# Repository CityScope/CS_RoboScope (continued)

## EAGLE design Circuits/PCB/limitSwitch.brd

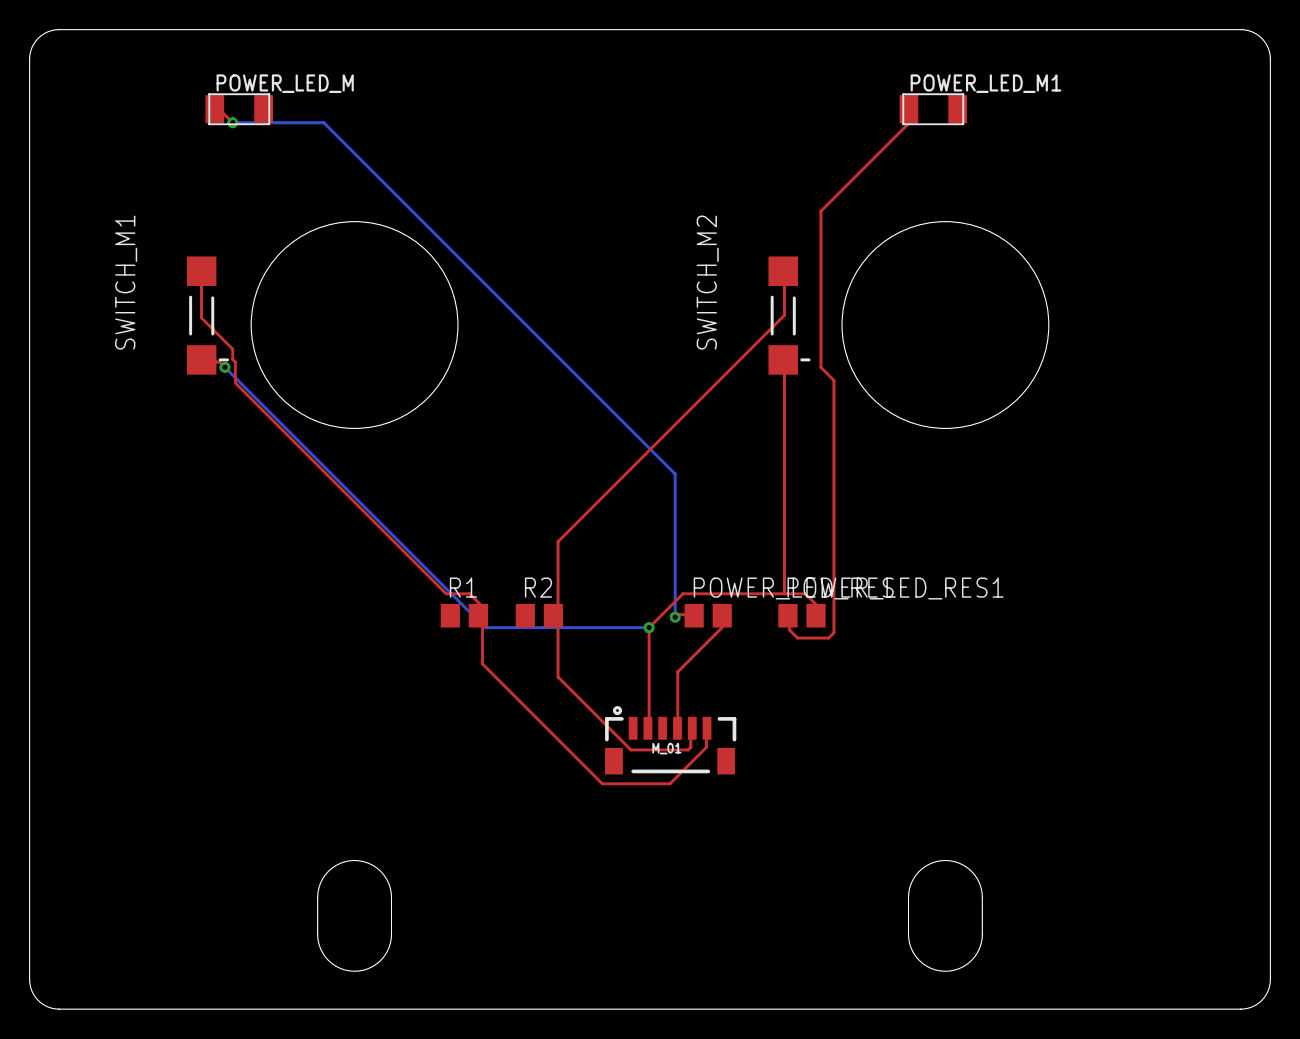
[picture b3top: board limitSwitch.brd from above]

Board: 2 copper layers, 84.0 x 66.3 mm, 9 parts (0 on the bottom side), 7 nets.

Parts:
M_01: 1X06-1MM
POWER_LED_M, POWER_LED_M1: LEDFAB1206; LED1206FAB
POWER_LED_RES, POWER_LED_RES1: 500; M0805
R1, R2: 10k; M0805
SWITCH_M1, SWITCH_M2: DTSM-3

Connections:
GND_MCU: M_01.1, POWER_LED_M.2, POWER_LED_M1.2, R1.1, R2.1
LED_IN: M_01.4, POWER_LED_RES.2
unnamed: POWER_LED_M1.1, POWER_LED_RES1.1
unnamed: POWER_LED_M.1, POWER_LED_RES.1
SWITCH_01: M_01.6, R1.2, SWITCH_M1.2
SWITCH_02: M_01.5, R2.2, SWITCH_M2.2
VCC_MCU: M_01.2, POWER_LED_RES1.2, SWITCH_M1.1, SWITCH_M2.1

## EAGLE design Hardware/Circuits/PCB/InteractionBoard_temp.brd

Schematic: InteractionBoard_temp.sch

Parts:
C1, C2, C3, C4, C5, C6, C7, C8, C9: 0.1uF; 0603-CAP
J3: F-2X10-DIL-2MM; DIL-2MM-2X10
JP1: JUMPER-SMT_3_1-NC_TRACE_NO-SILK; SMT-JUMPER_3_1-NC_TRACE_NO-SILK
JP6, JP7, JP8, JP9, JP10, JP11: JUMPER-SMT_2_NC_TRACE_NO-SILK; SMT-JUMPER_2_NC_TRACE_NO-SILK
M_01, M_02, M_03, M_04, M_05, M_06, M_07, M_08: CONN_06SMD-1MM; 1X06-1MM
POWE_3.3: LEDFAB1206; LED1206FAB
R1, R2, R3, R5, R6, R7, R8: 10k; M0805
R4: 10K; M0805
R9, R10, R11, R12, R13, R14, R16, R17, R18, R19, R20, R21, R23, R24, R25, R26: 10K; 0603-RES
R27, R28: 500; 0603-RES
RN1, RN2, RN3: 4R-NEXB38V; EXB38V
S1: JS207011SCQNR; SW_JS207011SCQNR
S2: MOMENTARY-SWITCH-SPST-2-SMD-5.2MM; TACTILE_SWITCH_SMD_5.2MM
STATUS_LED: LEDFAB1206; LED1206FAB
SW1: 219-10; CTS-219-10
SWB_1, SWB_2, SWB_3, SWB_4, SWB_5, SWB_6, SWB_7, SWB_8: B3F-1000
SWITCH_M1, SWITCH_M2, SWITCH_M3, SWITCH_M4, SWITCH_M5, SWITCH_M6, SWITCH_M7, SWITCH_M8: DTSM-3
SWR_1, SWR_2, SWR_3, SWR_4, SWR_5, SWR_6, SWR_7, SWR_8: 10K; M0805
U1, U2, U4: SX1509; QFN-28

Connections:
0_SX1: M_04.6, U1.27 (I/O[0])
0_SX2: M_08.6, U2.27 (I/O[0])
0_SX3: U4.27 (I/O[0])
1_SX1: M_04.5, U1.28 (I/O[1])
1_SX2: M_08.5, U2.28 (I/O[1])
1_SX3: J3.16, U4.28 (I/O[1])
2_SX1: M_02.6, U1.1 (I/O[2])
2_SX2: M_06.6, U2.1 (I/O[2])
2_SX3: J3.14, U4.1 (I/O[2])
3.3V: C1.1, C2.1, C3.1, C4.1, C5.1, C6.1, C7.1, C8.1, C9.1, J3.19, R9.2, R10.2, R11.2, R12.2, R13.2, R14.2, R16.2, R17.2, R18.2, R19.2, R20.2, R21.2, R23.2, R24.2, R25.2, R26.2, R27.2, RN1.5 (2), RN1.6 (2), RN1.7 (2), RN1.8 (2), RN2.7 (2), RN2.8 (2), RN3.5 (2), RN3.6 (2), RN3.7 (2), RN3.8 (2), S2.1, S2.2, SWB_1.1, SWB_2.1, SWB_3.1, SWB_4.1, SWB_5.1, SWB_6.1, SWB_7.1, SWB_8.1, SWITCH_M1.1, SWITCH_M2.1, SWITCH_M3.1, SWITCH_M4.1, SWITCH_M5.1, SWITCH_M6.1, SWITCH_M7.1, SWITCH_M8.1, U1.4 (VCC1), U1.12 (VDDM), U1.18 (VCC2), U2.4 (VCC1), U2.12 (VDDM), U2.18 (VCC2), U4.4 (VCC1), U4.12 (VDDM), U4.18 (VCC2)
3_SX1: M_02.5, U1.2 (I/O[3])
3_SX2: M_06.5, U2.2 (I/O[3])
3_SX3: J3.12, U4.2 (I/O[3])
4_SX1: M_02.4, U1.5 (I/O[4])
4_SX2: M_06.4, U2.5 (I/O[4])
4_SX3: JP1.1, U4.5 (I/O[4])
5_SX1: M_04.4, U1.6 (I/O[5])
5_SX2: M_08.4, U2.6 (I/O[5])
5_SX3: R28.2, U4.6 (I/O[5])
6_SX1: R2.2, SWB_2.3, SWITCH_M2.2, SWR_2.2, U1.7 (I/O[6])
6_SX2: R6.2, SWB_6.3, SWITCH_M6.2, SWR_6.2, U2.7 (I/O[6])
6_SX3: RN1.1, SW1.20, U4.7 (I/O[6])
7_SX1: R4.2, SWB_4.3, SWITCH_M4.2, SWR_4.2, U1.8 (I/O[7])
7_SX2: R8.2, SWB_8.3, SWITCH_M8.2, SWR_8.2, U2.8 (I/O[7])
7_SX3: RN1.2 (1), SW1.19, U4.8 (I/O[7])
8_SX1: R1.2, SWB_1.3, SWITCH_M1.2, SWR_1.2, U1.13 (I/O[8])
8_SX2: R5.2, SWB_5.3, SWITCH_M5.2, SWR_5.2, U2.13 (I/O[8])
8_SX3: RN1.3 (1), SW1.18, U4.13 (I/O[8])
9_SX1: R3.2, SWB_3.3, SWITCH_M3.2, SWR_3.2, U1.14 (I/O[9])
9_SX2: R7.2, SWB_7.3, SWITCH_M7.2, SWR_7.2, U2.14 (I/O[9])
9_SX3: RN1.4 (1), SW1.17, U4.14 (I/O[9])
10_SX1: M_01.6, U1.15 (I/O[10])
10_SX2: M_05.6, U2.15 (I/O[10])
10_SX3: RN3.1, SW1.16, U4.15 (I/O[10])
11_SX1: M_01.5, U1.16 (I/O[11])
11_SX2: M_05.5, U2.16 (I/O[11])
11_SX3: RN3.2 (1), SW1.15, U4.16 (I/O[11])
12_SX1: M_01.4, U1.19 (I/O[12])
12_SX2: M_05.4, U2.19 (I/O[12])
12_SX3: RN3.3 (1), SW1.14, U4.19 (I/O[12])
13_SX1: M_03.6, U1.20 (I/O[13])
13_SX2: M_07.6, U2.20 (I/O[13])
13_SX3: RN3.4 (1), SW1.13, U4.20 (I/O[13])
14_SX1: M_03.5, U1.21 (I/O[14])
14_SX2: M_07.5, U2.21 (I/O[14])
14_SX3: RN2.1, SW1.12, U4.21 (I/O[14])
15_SX1: M_03.4, U1.22 (I/O[15])
15_SX2: M_07.4, U2.22 (I/O[15])
15_SX3: RN2.2 (1), SW1.11, U4.22 (I/O[15])
!INT_SX3: R24.1, U4.9 (!INT)
!RESET_SX1: R9.1, U1.23 (!RESET)
!RESET_SX2: R16.1, U2.23 (!RESET)
!RESET_SX3: R14.1, U4.23 (!RESET)
ADDR0_SX1: JP8.1, U1.26 (ADDR0)
ADDR0_SX2: JP7.1, U2.26 (ADDR0)
ADDR0_SX3: JP11.1, U4.26 (ADDR0)
ADDR1_SX1: JP9.1, U1.10 (ADDR1)
ADDR1_SX2: JP6.1, U2.10 (ADDR1)
ADDR1_SX3: JP10.1, U4.10 (ADDR1)
GND_MCU: C1.2, C2.2, C3.2, C4.2, C5.2, C6.2, C7.2, C8.2, C9.2, J3.18, J3.20, JP7.2, JP9.2, M_01.1, M_02.1, M_03.1, M_04.1, M_05.1, M_06.1, M_07.1, M_08.1, POWE_3.3.2 (C), R1.1, R2.1, R3.1, R4.1, R5.1, R6.1, R7.1, R8.1, RN2.3 (1), STATUS_LED.2 (C), SW1.1, SW1.2, SW1.3, SW1.4, SW1.5, SW1.6, SW1.7, SW1.8, SW1.9, SW1.10, SWR_1.1, SWR_2.1, SWR_3.1, SWR_4.1, SWR_5.1, SWR_6.1, SWR_7.1, SWR_8.1, U1.3 (GND), U1.17 (GND), U1.29 (GND), U2.3 (GND), U2.17 (GND), U2.29 (GND), U4.3 (GND), U4.17 (GND), U4.29 (GND)
INT_01: J3.6, R12.1, U1.9 (!INT)
INT_02: J3.8, R19.1, U2.9 (!INT)
unnamed: JP6.2, R21.1
unnamed: JP8.2, R13.1
unnamed: R28.1, STATUS_LED.1 (A)
unnamed: JP10.2, R25.1
unnamed: JP11.2, R26.1
unnamed: POWE_3.3.1 (A), R27.1
NEOPIXEL_01: J3.1, M_01.3
NEOPIXEL_02: J3.3, M_02.3
NEOPIXEL_03: J3.5, M_03.3
NEOPIXEL_04: J3.7, M_04.3
NEOPIXEL_05: J3.9, M_05.3
NEOPIXEL_06: J3.11, M_06.3
NEOPIXEL_07: J3.13, M_07.3
NEOPIXEL_08: J3.15, M_08.3
OSCIO_SX1: U1.11 (OSCIO)
OSCIO_SX2: U2.11 (OSCIO)
OSCIO_SX3: U4.11 (OSCIO)
RESET: J3.10, JP1.2, JP1.3, RN2.6 (2), S2.3, S2.4
SCL_00: J3.4, R11.1, R18.1, R23.1, U1.25 (SCL), U2.25 (SCL), U4.25 (SCL)
SDA_00: J3.2, R10.1, R17.1, R20.1, U1.24 (SDA), U2.24 (SDA), U4.24 (SDA)
VCC_5V: M_01.2, M_02.2, M_03.2, M_04.2, M_05.2, M_06.2, M_07.2, M_08.2, S1.4, S1.8
VCC_5V_IN: J3.17, S1.3, S1.7

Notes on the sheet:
INPUTS
Input power line for the BRD
I2C MUX
SWITCH
CONNECTORS
INFO
The VCC1/2 jumpers (SJ2, SJ3) set those pins to 3.3V.
I2C Address Select
VDD Range: 1.425-3.6V
Allowable VCC1/2 Range: 1.2-3.6V
IC2 MUX 01
IC2 MUX 02
IC2 MUX 03

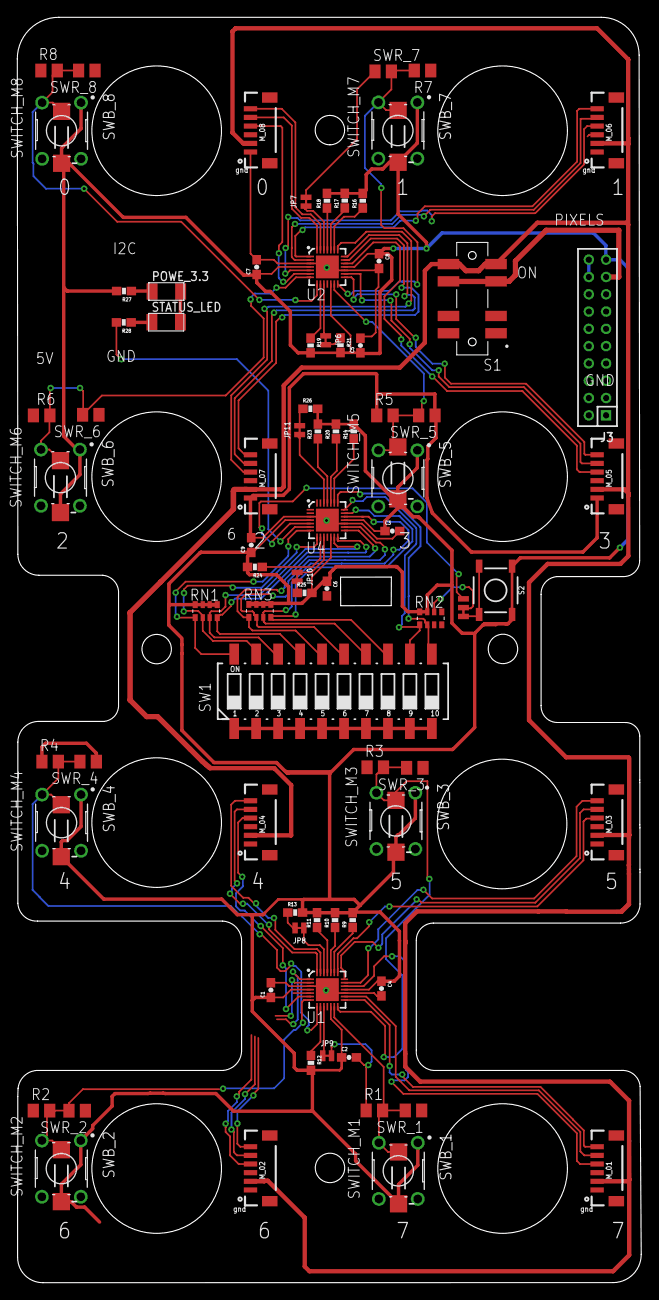
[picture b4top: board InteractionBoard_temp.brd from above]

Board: 2 copper layers, 72.1 x 146.3 mm, 86 parts (0 on the bottom side), 80 nets.
